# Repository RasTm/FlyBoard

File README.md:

Bu proje uçuş kontrol kartımız için gerekli yazılımım içermektedir. Proje tamamlandıkça bu bölüm kullanım klavuzu olarak değiştirilecektir.

Projeyi Atollic ile derleyebilmek için aşağıdaki işlemler yapılmalıdır.

1- Proje açılırken executable değil makefile olarak açılmalıdır.

2- C++ sürümü Properties (Alt+Enter) / C,C++ Build / Settings / Tool Settings / C++ Compiler / General başlığı altından C++ 11 olarak ayarlanmalıdır.

3- Properties (Alt+Enter) / C,C++ General / Paths and Symbols başlığına gidilip Includes, Library Paths, Source Location sekmelerine Libs klasörü eklenmelidir.

4- Properties (Alt+Enter) / C,C++ General / Paths and Symbols başlığına gidilip Includes ve Symbols sekmelerinden STD_Lib ile alakalı her şey kaldırılmalıdır. 

5- Libraries klasöründeki STD_periph klasörü kaldırılmalıdır. 

6- Libraries/Cmsis klasörü içerisine DSP_Lib ve Include klasörleri atılmalıdır eğer uyarı verirse orijinal dosyaların üzerine yazılmalıdır.

7- stm32f4xx_conf.h dosyasında eklenmiş tüm Stdlib kütüphaneleri kaldırılmalıdır.

8- Float değerleri LCD ekran üzerine yazdırmak için snprint fonksiyonu modifiye edilmelidir. Bunun için Properties (Alt+Enter) / C,C++ Build / Settings / Tool Settings / C++ Linker başlığı içerisinde Command alt başlığına "-u_printf_float" ifadesi yazılmalıdır.

9- Debug ekranında başlatmadan önce main'de durmasını sağlayan breakpoint kaldırılmalı yoksa C++ ile geliştirme yaparken program kırılabilir. Kaldırmak için Configure Debug / Startup Scripts gidilmeli. Buranın en altından 
"# Set a breakpoint at main(). tbreak main" Silinmeli.

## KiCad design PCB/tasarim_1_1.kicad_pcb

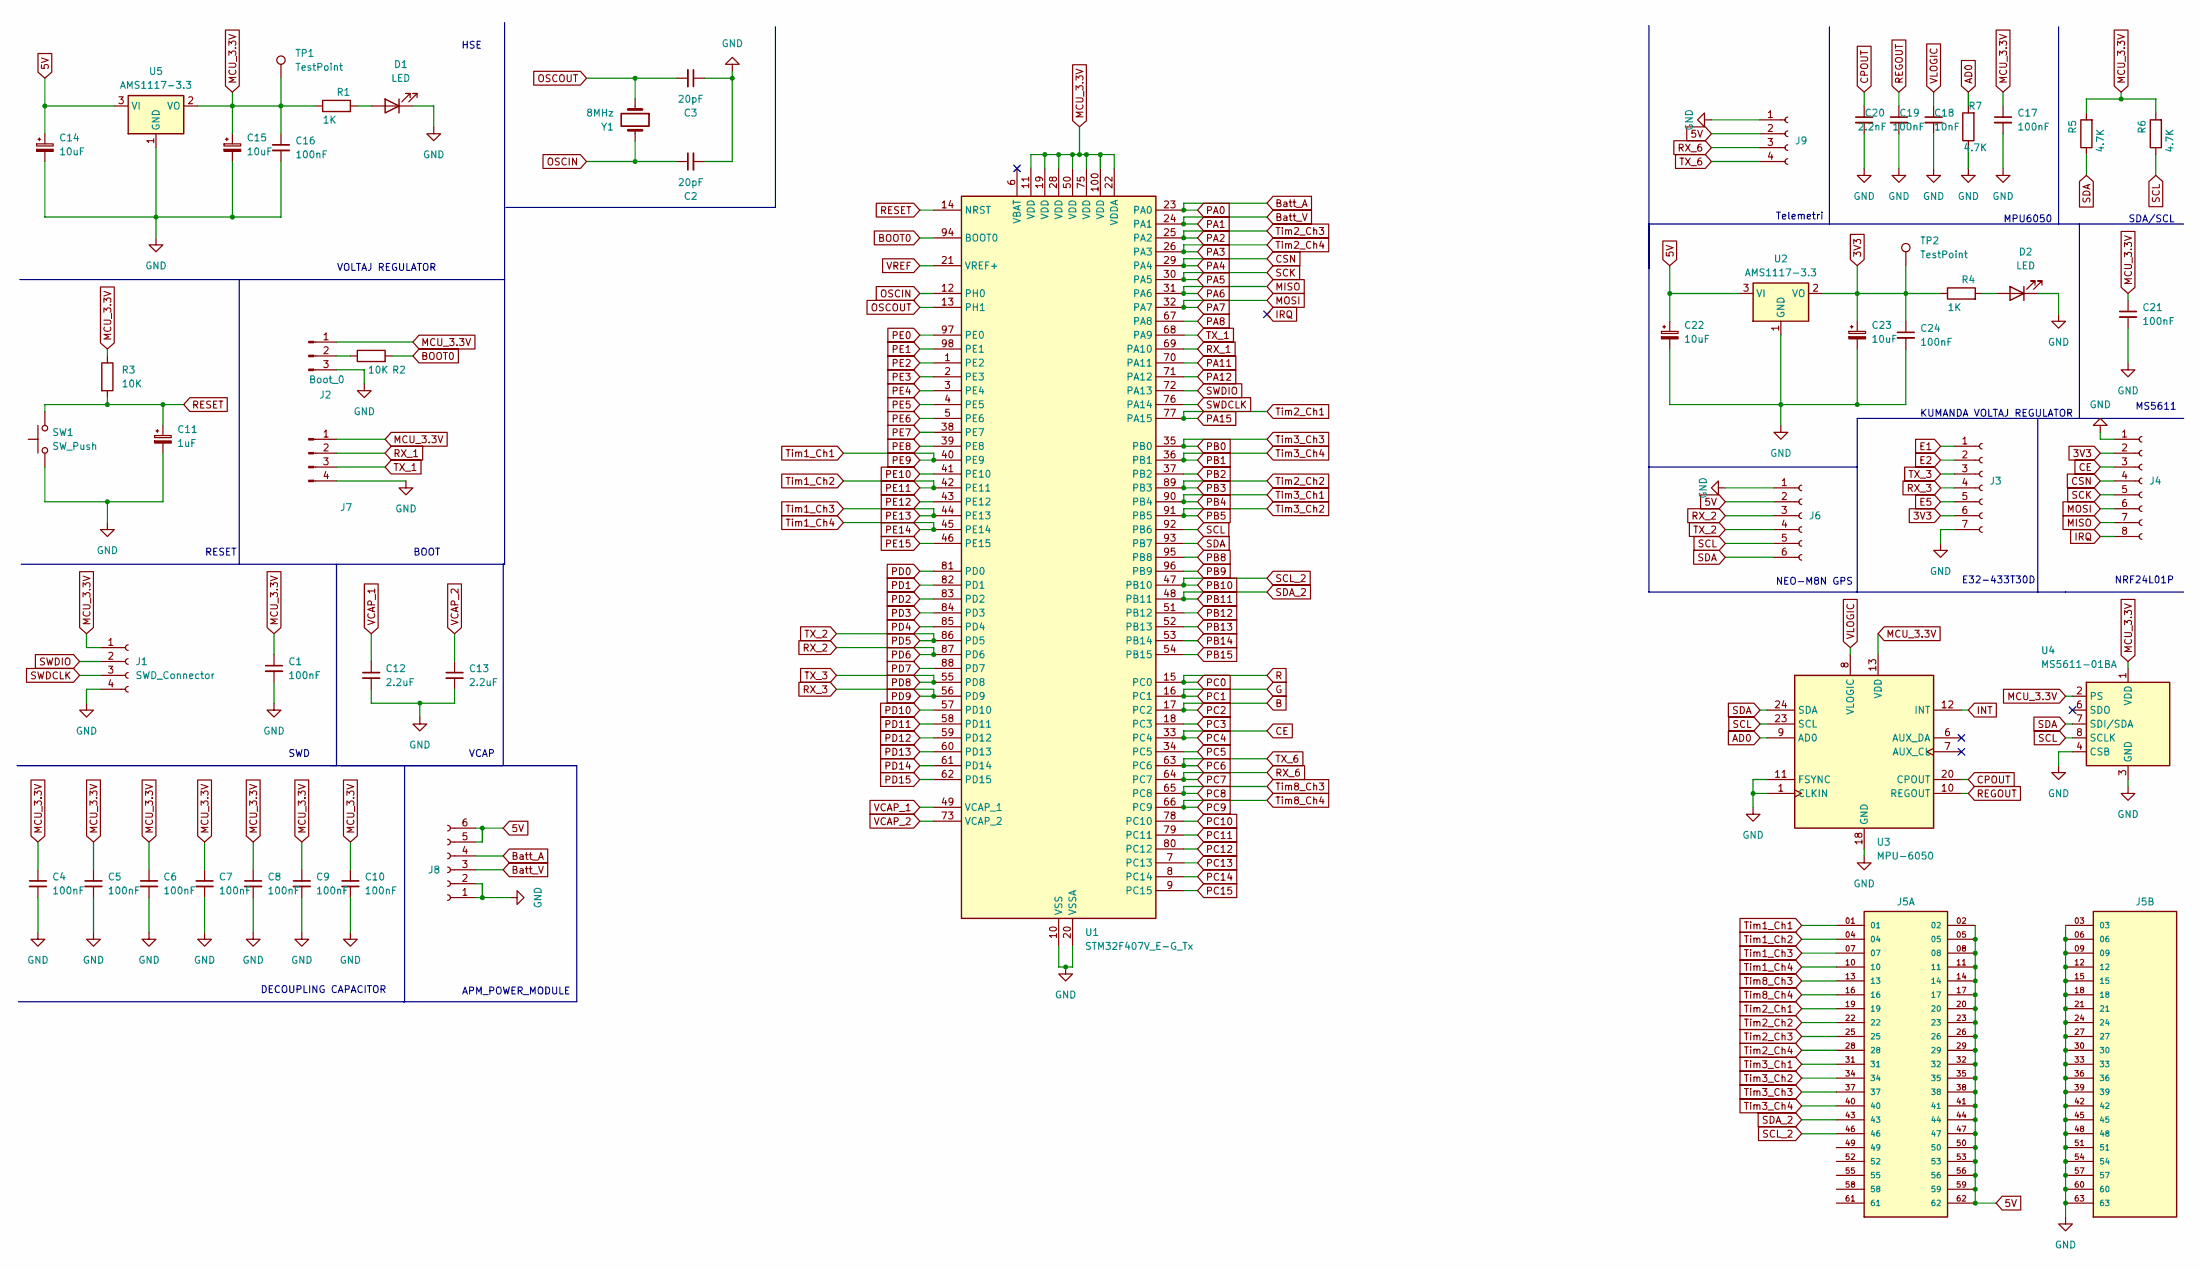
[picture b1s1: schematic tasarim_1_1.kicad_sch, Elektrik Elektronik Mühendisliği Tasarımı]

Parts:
C1, C4, C5, C6, C7, C8, C9, C10, C16, C17, C19, C21, C24: 100nF; C_0603_1608Metric
C2, C3: 20pF; C_0603_1608Metric
C11: 1uF; CP_EIA-1608-08_AVX-J
C12, C13: 2.2uF; CP_EIA-1608-08_AVX-J
C14, C15, C22, C23: 10uF; CP_EIA-1608-08_AVX-J
C18: 10nF; C_0603_1608Metric
C20: 2.2nF; C_0603_1608Metric
D1, D2: LED; LED_0805_2012Metric
J1: SWD_Connector; PinHeader_1x04_P2.54mm_Horizontal
J2: Boot_0; PinHeader_1x03_P2.54mm_Vertical
J3: LORA_Connector; JST_PH_B7B-PH-K_1x07_P2.00mm_Vertical
J4: NRF_Connector; JST_PH_B8B-PH-K_1x08_P2.00mm_Vertical
J5: ZW-21-08-L-T-200-157; SAMTEC_ZW-21-08-L-T-200-157; PARTREV R
J6: GPS_Connector; Hirose_DF13-06P-1.25DSA_1x06_P1.25mm_Vertical
J7: Bootloader_Port; PinHeader_1x04_P2.54mm_Vertical
J8: APM_Connector; Hirose_DF13-06P-1.25DSA_1x06_P1.25mm_Vertical
J9: Telemetri; JST_PH_B4B-PH-K_1x04_P2.00mm_Vertical
R1, R4: 1K; R_0603_1608Metric
R2, R3: 10K; R_0603_1608Metric
R5, R6, R7: 4.7K; R_0603_1608Metric
SW1: SW_Push; SW_PUSH_6mm_H5mm
TP1, TP2: TestPoint; TestPoint_Pad_D1.0mm
U1: STM32F407V_E-G_Tx; LQFP-100_14x14mm_P0.5mm
U2, U5: AMS1117-3.3; SOT-223-3_TabPin2
U3: MPU-6050; InvenSense_QFN-24_4x4mm_P0.5mm
U4: MS5611-01BA; LGA-8_3x5mm_P1.25mm
Y1: 8MHz; Crystal_HC49-4H_Vertical

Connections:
3V3: C23.1, C24.1, J3.6, J4.2, R4.1, TP2.1, U2.2 (VO)
5V: C14.1, C22.1, J5.02, J5.05, J5.08, J5.11, J5.14, J5.17, J5.20, J5.23, J5.26, J5.29, J5.32, J5.35, J5.38, J5.41, J5.44, J5.47, J5.50, J5.53, J5.56, J5.59, J5.62, J6.2, J8.5, J8.6, J9.2, U2.3 (VI), U5.3 (VI)
AD0: R7.2, U3.9 (AD0)
B: U1.17 (PC2)
BOOT0: R2.2, U1.94 (BOOT0)
Batt_A: J8.4, U1.23 (PA0)
Batt_V: J8.3, U1.24 (PA1)
CE: J4.3, U1.33 (PC4)
CPOUT: C20.1, U3.20 (CPOUT)
CSN: J4.4, U1.29 (PA4)
E1: J3.1
E2: J3.2
E5: J3.5
G: U1.16 (PC1)
GND: C1.2, C2.2, C3.1, C4.2, C5.2, C6.2, C7.2, C8.2, C9.2, C10.2, C11.2, C12.2, C13.2, C14.2, C15.2, C16.2, C17.2, C18.2, C19.2, C20.2, C21.2, C22.2, C23.2, C24.2, D1.1 (K), D2.1 (K), J1.4, J2.3, J3.7, J4.1, J5.03, J5.06, J5.09, J5.12, J5.15, J5.18, J5.21, J5.24, J5.27, J5.30, J5.33, J5.36, J5.39, J5.42, J5.45, J5.48, J5.51, J5.54, J5.57, J5.60, J5.63, J6.1, J7.4, J8.1, J8.2, J9.1, R7.1, SW1.1, U1.10 (VSS), U1.20 (VSSA), U1.27 (VSS), U1.74 (VSS), U1.99 (VSS), U2.1 (GND), U3.1 (CLKIN), U3.11 (FSYNC), U3.18 (GND), U4.3 (GND), U4.4 (CSB), U4.5 (CSB), U5.1 (GND)
INT: U3.12 (INT)
IRQ: J4.8
MCU_3.3V: C1.1, C4.1, C5.1, C6.1, C7.1, C8.1, C9.1, C10.1, C15.1, C16.1, C17.1, C21.1, J1.1, J2.1, J7.1, R1.1, R3.1, R5.2, R6.2, TP1.1, U1.11 (VDD), U1.19 (VDD), U1.22 (VDDA), U1.28 (VDD), U1.50 (VDD), U1.75 (VDD), U1.100 (VDD), U3.13 (VDD), U4.1 (VDD), U4.2 (PS), U5.2 (VO)
MISO: J4.7, U1.31 (PA6)
MOSI: J4.6, U1.32 (PA7)
unnamed: D1.2 (A), R1.2
unnamed: D2.2 (A), R4.2
unnamed: J2.2, R2.1
OSCIN: C2.1, U1.12 (PH0), Y1.2
OSCOUT: C3.2, U1.13 (PH1), Y1.1
PA2: J5.25, U1.25 (PA2)
PA3: J5.28, U1.26 (PA3)
PA5: J4.5, U1.30 (PA5)
PA8: U1.67 (PA8)
PA11: U1.70 (PA11)
PA12: U1.71 (PA12)
PA15: J5.19, U1.77 (PA15)
PB0: J5.37, U1.35 (PB0)
PB1: J5.40, U1.36 (PB1)
PB2: U1.37 (PB2)
PB3: J5.22, U1.89 (PB3)
PB4: J5.31, U1.90 (PB4)
PB5: J5.34, U1.91 (PB5)
PB8: U1.95 (PB8)
PB9: U1.96 (PB9)
PB10: J5.46, U1.47 (PB10)
PB11: J5.43, U1.48 (PB11)
PB12: U1.51 (PB12)
PB13: U1.52 (PB13)
PB14: U1.53 (PB14)
PB15: U1.54 (PB15)
PC0: U1.15 (PC0)
PC3: U1.18 (PC3)
PC5: U1.34 (PC5)
PC6: J9.4, U1.63 (PC6)
PC7: J9.3, U1.64 (PC7)
PC8: J5.13, U1.65 (PC8)
PC9: J5.16, U1.66 (PC9)
PC10: U1.78 (PC10)
PC11: U1.79 (PC11)
PC12: U1.80 (PC12)
PC13: U1.7 (PC13)
PC14: U1.8 (PC14)
PC15: U1.9 (PC15)
PD0: U1.81 (PD0)
PD1: U1.82 (PD1)
PD2: U1.83 (PD2)
PD3: U1.84 (PD3)
PD4: U1.85 (PD4)
PD5: J6.4, U1.86 (PD5)
PD6: J6.3, U1.87 (PD6)
PD7: U1.88 (PD7)
PD8: J3.3, U1.55 (PD8)
PD9: J3.4, U1.56 (PD9)
PD10: U1.57 (PD10)
PD11: U1.58 (PD11)
PD12: U1.59 (PD12)
PD13: U1.60 (PD13)
PD14: U1.61 (PD14)
PD15: U1.62 (PD15)
PE0: U1.97 (PE0)
PE1: U1.98 (PE1)
PE2: U1.1 (PE2)
PE3: U1.2 (PE3)
PE4: U1.3 (PE4)
PE5: U1.4 (PE5)
PE6: U1.5 (PE6)
PE7: U1.38 (PE7)
PE8: U1.39 (PE8)
PE9: J5.01, U1.40 (PE9)
PE10: U1.41 (PE10)
PE11: J5.04, U1.42 (PE11)
PE12: U1.43 (PE12)
PE13: J5.07, U1.44 (PE13)
PE14: J5.10, U1.45 (PE14)
PE15: U1.46 (PE15)
REGOUT: C19.1, U3.10 (REGOUT)
RESET: C11.1, R3.2, SW1.2, U1.14 (NRST)
RX_1: J7.2, U1.69 (PA10)
SCL: J6.5, R6.1, U1.92 (PB6), U3.23 (SCL), U4.8 (SCLK)
SDA: J6.6, R5.1, U1.93 (PB7), U3.24 (SDA), U4.7 (SDI/SDA)
SWDCLK: J1.3, U1.76 (PA14)
SWDIO: J1.2, U1.72 (PA13)
TX_1: J7.3, U1.68 (PA9)
VCAP_1: C12.1, U1.49 (VCAP_1)
VCAP_2: C13.1, U1.73 (VCAP_2)
VLOGIC: C18.1, U3.8 (VLOGIC)
VREF: U1.21 (VREF+)

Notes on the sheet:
VCAP
RESET
DECOUPLING CAPACITOR
HSE
SWD
MPU6050
BOOT
NEO-M8N GPS
APM_POWER_MODULE
NRF24L01P
Telemetri
E32-433T30D
MS5611
KUMANDA VOLTAJ REGULATOR
VOLTAJ REGULATOR
SDA/SCL

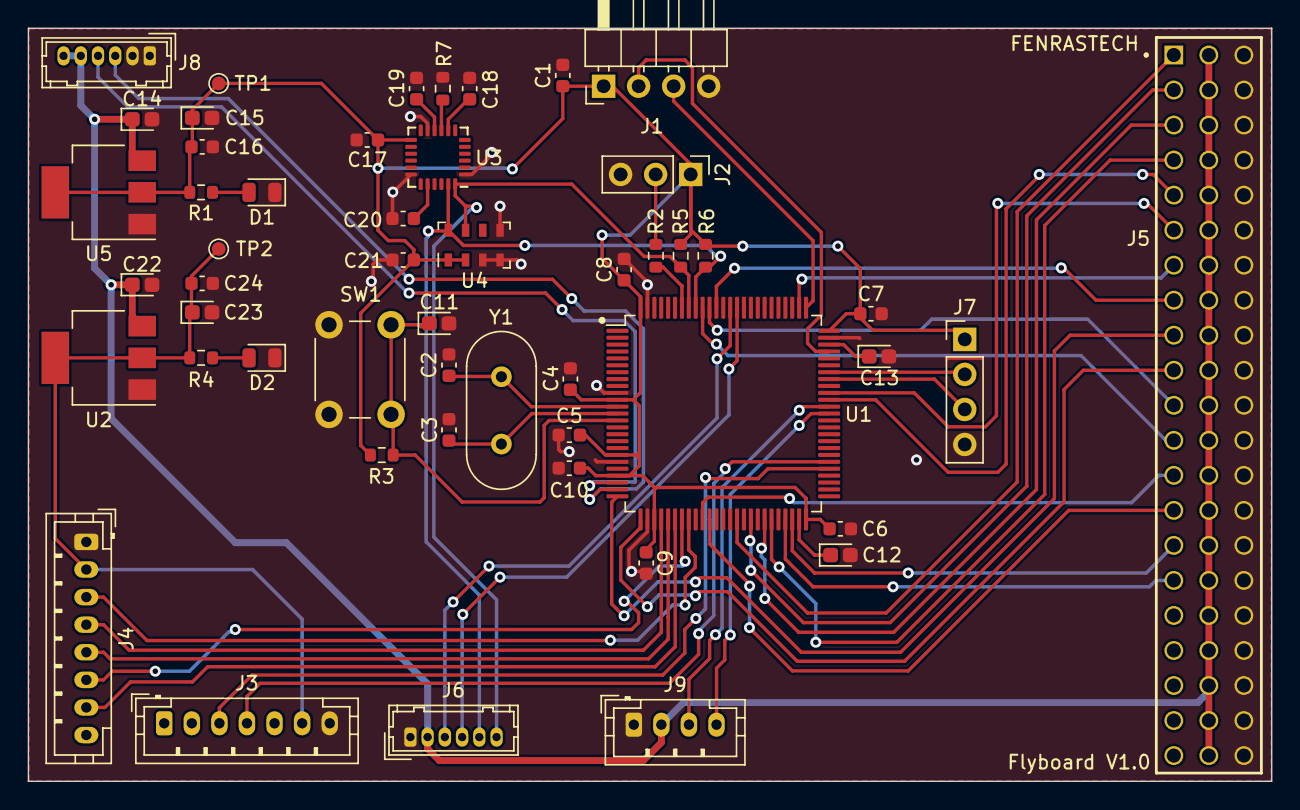
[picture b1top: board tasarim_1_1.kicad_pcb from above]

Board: 2 copper layers, 90.2 x 54.6 mm, 51 parts (0 on the bottom side), 52 nets.

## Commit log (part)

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2021-02-11 FlyBoard
2024-07-18 new make
2024-07-19 git commit -m"asdf" modified: src/main.cpp
2024-07-20 ms5611
    ms5611 + mpu6050
2024-07-20 readme
2024-07-22 compass
2024-07-23 compass .hpp update
2024-08-09 hmc lib config
2024-11-23 dsp
    dsp lib
2025-01-26 laptop format
2025-01-26 few2
2025-03-22 variable name changes
2025-03-22 Gyro Formula Fix
2025-03-22 Minor Fix, Hz calculation
    MPU6050 calculation loop frequency measurement
2025-03-23 MPU6050 library vector optimization
2025-03-23 mpu and ms library arrangement
    command line arrangement
    new class variables and using in methods
    make simpler main.cpp
2025-03-23 new dsp lib included
2025-03-23 Squash merge dsp into master
2025-03-25 program counter fix
    uint8_t changed to uint32_t
2025-03-25 new merge
2025-03-25 comment line spacing fix
2025-03-28 Flyboard V1.0 PCB
    KiCAD PCB files
2025-03-30 ms5611 minor fix
    if-if changed to if-else
2025-04-07 volatile
2025-04-13 Uart 6 connect to ST-LINK V2
    so we need to change baud rate to 9600
2025-04-13 minox bug fixes
2025-04-13 mpu6050 adjustment
2025-04-14 New Template Function Added
2025-04-14 add old style usart template func for memory optimization
2025-04-14 minor changes
2025-04-14 minor optimization
2025-04-14 program management intrrupt fix, baud rate fix for low Hz
2025-04-15 Fake Sensor I2C Address Update
2025-04-15 minor fix
2025-04-15 systick timer minor fix
2025-04-15 comment line fix
2025-04-15 comment line added
2025-04-15 hmc5883L added
2025-04-17 last main before pointers
    change management of program with pointers
2025-04-17 start to dev pointer program management
2025-04-19 ı dont know
2025-04-19 minor fix in lib
2025-05-01 program buffer update
2025-05-01 small optimization on hmc
2025-05-03 Add new fake HMC5883 Lib, fix HMC5883 Lib, minor fix in MS5611
2025-05-03 buffer updated
2025-05-08 smoll comment fix
2025-05-08 smoll changes
2025-05-08 add new data ready status for QMC5883
2025-05-18 back normal again
2025-05-18 QMC5883L library created
2025-05-18 some optimization
2025-05-18 PCB test main code
2025-05-19 add new false reading safeguard for ms5611
2025-05-24 add new functions, optimize current functions and names
2025-05-24 add new functions, and change function names
2025-05-24 update bcz of gpio lib
2025-05-24 few optimizations
2025-05-24 few opt
2025-05-24 new i2c recover function added
    i2c recover function does i2c pin high and reset so it prevents to
    locking i2c situations
2025-05-26 solve interrupt priority problem
2025-05-26 add new ppm decoder code begining
2025-05-29 new ppm decoder lib
2025-05-29 ppm decoder added
2025-05-29 tim13 stops when debug hits breakpoint
2025-05-31 small optimization
2025-05-31 i2c recover added inside the library
2025-05-31 unused functions removed
2025-05-31 new ppm interrupt
2025-06-01 solve sensor malfunction with software
2025-06-01 add new ppm failsafe feature
2025-06-01 ppm failsafe uses tim13 update interrupt
2025-06-02 new adc configuration and new static functions added
2025-06-02 better optimization for ms5611
2025-06-02 for clean main some variables carry into class
2025-06-02 new gps lib
2025-06-05 added new disable funcitons in ADC lib
2025-06-05 new adc read tryout
2025-06-05 asdf
2025-06-09 new adc dma function added
2025-06-09 dma 1 and 2 clocks enable
2025-06-09 new adc dma readings added
2025-06-20 some changes
2025-06-20 uart rx lines pull up
2025-06-20 new adc, dma and more
2025-06-21 new lines from system_init()
2025-06-21 program counters go volatile
2025-06-24 telemetry code
2025-06-24 fdsa
2025-08-30 zort
2025-08-30 delete
2025-12-12 main.h added
    main.h added, i2c periph fast mode update, dma periph driver starting
    develop
2025-12-22 small changes
    gpio reset function improved
    i2c improved
    i2c used sensor functions improved
2025-12-23 Systick and PPM decode update
    Systick priority change
    PPM decode (uin16_t) change and some comment line
2026-06-14 new readme and dsp files
2026-06-14 new kicad version update
